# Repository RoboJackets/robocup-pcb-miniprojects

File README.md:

# Robocup 2026 Onboarding Project

## Description

This is the main repo for the 2026 onboarding season of Robojackets Robocup.

## Setup

Have ONE member of your team do this:

```sh
git clone https://github.com/RoboJackets/robocup-pcb-miniprojects
cd robocup-pcb-miniprojects
git checkout -b <your-team-name>
git push -u origin <your-team-name>
```

Now ALL members can:

```sh
git clone https://github.com/RoboJackets/robocup-pcb-miniprojects
cd robocup-pcb-miniprojects
git checkout <your-team-name>
```

This branch is where all work for your project should be done. Do not attempt to modify main, and especially do not try to modify other teams' branches.

## Overview

Your task is to create a daisy-chained sensor suite. Powered by the RP2040, this should be able to take a data packet from an SPI input, add to this packet, and pass it to the next board via SPI. Information for this packet is to be collected from the six distinct I2C devices on the board.

### PCB
Your KiCAD project folder and all other relevant files should be stored in [pcb](/pcb/).

See the [README](/pcb/README.md) for specific information.

### Firmware
Your Pico SDK project folder and all other relevant files should be stored in [firmware](/firmware/).

See the [README](/firmware/README.md) for specific information.

### Documentation

All live documentation (Hardware Reference Manuals, Technical Overviews, etc) should be stored in your team's drive folder which can be found [HERE](https://drive.google.com/drive/folders/1aSuq1g-BM3DlAOSG3E911sSWYeNv8i6k?usp=drive_link).

Start by copying the two template files from the project template folder [HERE](https://drive.google.com/drive/folders/1uaQHIUm1E482NEQLdI7As42oW3_wIS3i?usp=drive_link).

## Additional Notes

Project updates will be added here as needed

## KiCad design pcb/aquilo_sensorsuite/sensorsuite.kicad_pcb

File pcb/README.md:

# Daisy-Chained Sensor Suite PCB

## Overview

You will be planning, designing, and laying out the PCB for a daisy-chainable sensor suite. The core features of this board will be a RP2040 MCU, Micro USB programming/power input, SPI I/O, and six I2C peripherals.

## Requirements

Additional design specifications can be found in the Hardware Reference Manual (HRM).

1. Documentation
    - While most major parts are pre-selected for you, the documentation for these has not been. You will need to finish filling out the missing sections in the HRM for each component.
    - If you add any new components with a major impact on the final product, make sure to include them as well
    - Overall, keep your HRM as up to date as possible with as much important information as possible so your firmware team can progress along side you
2. PCB
    - Must be manufacturable
        - See JLCPCB capabilities [HERE](https://jlcpcb.com/capabilities/pcb-capabilities)
        - *Hint hint nudge nudge an option for board settings is to import from another board, and Robocup might have boards with similar design requirements [HERE](https://github.com/RoboJackets/robocup-pcb)*
    - Four layers max
        - Going below four is not recommended
    - Size
        - 80mm X 50mm
    - Must pass DRC
        - Will be checked with the Robocup standard DRC suite (if you followed the hint this likely will not be an issue)
    - Must consider signal integrity
    - Must have a legible and correct silkscreen
        - Labels by components or otherwise noted
        - Location for serial number
        - Identifier for all those who worked on it
        - Bonus points for fitting the Robojackets logo
    - Must meet overall required specifications
    - Must have 4 mounting holes (M2)
3. Schematic
    - Must utilize a hierarchy of sheets
        - Do not even ask for a design review of a schematic all crammed on one sheet it is not feasible for the expected complexity
        - Also do not excessively break into sub-sheets, consider what is seperate/repeatable enough to place in a sub-sheet.
    - Notate important characteristics in the schematic
        - General comments
        - Section functionality
        - Placement location requirements
        - Component relevant information
        - The less you have to check the HRM the better
    - Must fill out all sheet information in the right corner
        - Include an additional note for designer name
    - Symbol fields
        - You must fill out all default fields of major components. Non-specialized passives just need footprint and value
        - You must add the field "Vendor P/N" to every specific component with the value set to the Digikey part number
    - When you need to make/import new symbols/footprints/3D models, add them to a new custom library called "local" and store their files if needed in [lib](./lib/)
    - Maintain neatness and readability throughout the schematic
        - General signal flow should go left to right
        - Favor wire net labels over long track wires/grouped outputs
        - Group components by relation/usage
4. Power
    - Power must be able to come from both the USB port and the previous board's SPI line and they must never touch
        - See power MUXing
    - Your power must have appropriate protection for issues such as reverse voltage, ESD, shorts, etc.
    - Your total power draw, and expected power draw for six connected boards must be noted in your schematic and reflected in your protection circuits 
        - Note only one board with an LED array will be active at once
    - There must be some indication that power is connected to the board
5. I2C Devices
    - Must have all six I2C devices and their complementary circuits
        1. IMU
        2. Temperature Sensor
        3. Hall Effect Sensor
        4. GPIO expander
            - Connected to 8 switch DIP switch
            - Resistor network pullup
        5. Color Sensor
        6. LED PWM Controller
            - 8 RGB LEDs
    - Each device must have have different I2C lines
        - However they can share I2C buses
    - Do not use interrupt lines
        - Leave safely disconnected per design requirements
6. Interface
    - Must have at least two general purpose buttons
    - Must have at least three general purpose LEDs
    - Must have test points for all important voltage/signal sources
7. Overall
    - All parts must be in-stock at Digikey at time of completion
        - Yes, if stock runs out during the duration of the project this is still on you to catch
        - You can disregard this rule for parts from the Part Selection specification

## Specifications

### Part Selection

These parts have already been selected for you

- MCU: RP2040
    - 2648-SC0914(13)TR-ND
- 2MB Flash: W25Q16JVUXIQ TR
    - 256-W25Q16JVUXIQTR-ND
- 12MHz Crystal: ABM8-272-T3
    - 535-ABM8-272-T3TR-ND
- IMU: ICM-42605
    - 1428-1152-2-ND
- Color Sensor: VEML3328
    - 751-VEML3328TR-ND
- Hall Effect Sensor: TMAG5273A2QDBVR
    - 296-TMAG5273A2QDBVRTR-ND
- Temperature Sensor: LM75ADP
    - 568-4227-1-ND
- GPIO Expander: TCA9534PWR
    - 296-40574-2-ND
- DIP Switch: DS01C-254-L-08BE
    - 2223-DS01C-254-L-08BE-ND
- 10kOhm Resistor Network: YC158TJR-0710KL
    - 13-YC158TJR-0710KLTR-ND
- LED Controller: IS31FL3254-QFLS4-TR
    - 2521-IS31FL3254-QFLS4-TR-ND
- RGB LEDs: CLMVC-FKA-CL1D1L71BB7C3C3
    - CLMVC-FKA-CL1D1L71BB7C3C3TR-ND
- Micro USB Connector: 10118194-0001LF
    - 609-4618-2-ND
- SPI Connector: S6B-PH-K-S
    - 455-1723-ND
- 3.3V Linear Regulator: AP2112K-3.3
    - AP2112K-3.3TRG1DITR-ND
- OR Controller: LM66100DCKR
    - 296-53541-2-ND
- General Purpose LEDs (3)
    - 0603 LEDs
- General Purpose Buttons (2): SKRPABE010
    - 4809-SKRPABE010TR-ND

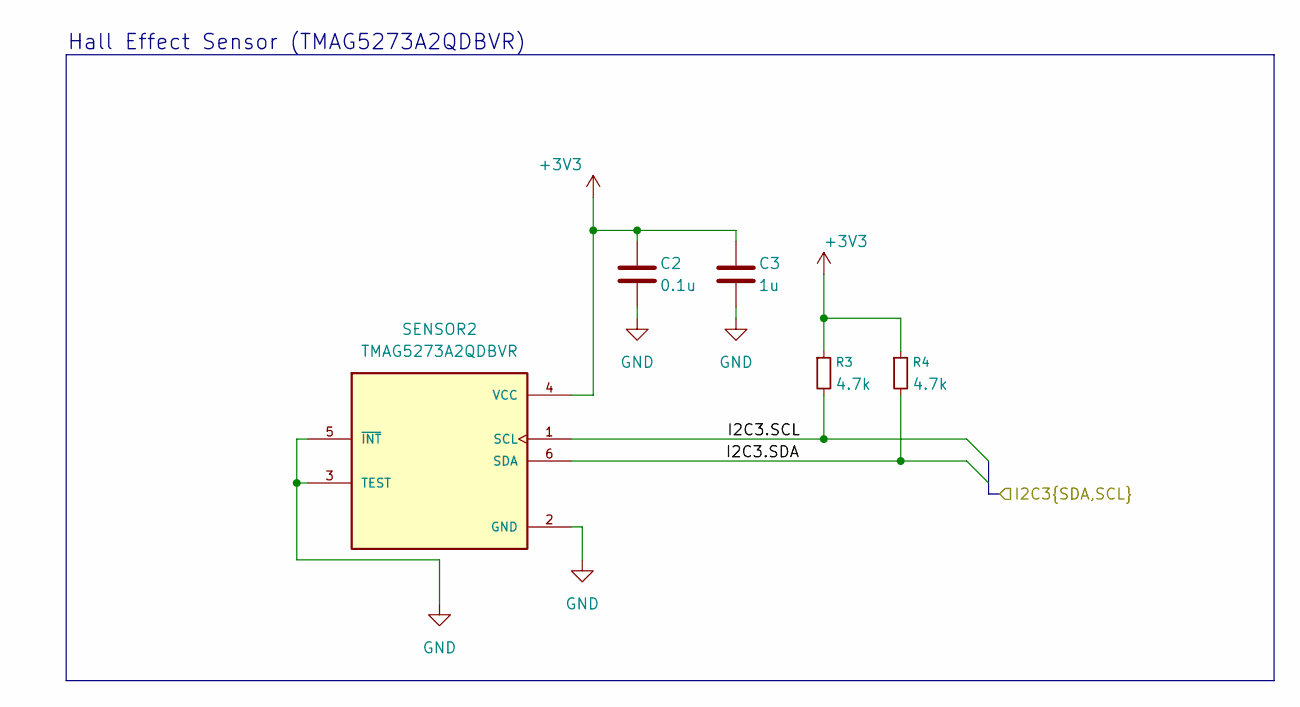
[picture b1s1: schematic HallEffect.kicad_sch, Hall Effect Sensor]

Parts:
C2: 0.1u; C_0402_1005Metric; Manufacturer P/N 0402B104K160HI
C3: 1u; C_0402_1005Metric; Manufacturer P/N 0402W105M6R3HI
R3, R4: 4.7k; R_0402_1005Metric; Manufacturer P/N RK73H1ETTP4701F
SENSOR2: TMAG5273A2QDBVR; SOT95P280X140-6N; Manufacturer P/N TMAG5273A2QDBVR

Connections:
+3V3: C2.1, C3.1, R3.1, R4.1, SENSOR2.4 (VCC); also elsewhere on the board
/Hall Effect Sensor/I2C3.SCL: R3.2, SENSOR2.1 (SCL); also elsewhere on the board
/Hall Effect Sensor/I2C3.SDA: R4.2, SENSOR2.6 (SDA); also elsewhere on the board
GND: C2.2, C3.2, SENSOR2.2 (GND), SENSOR2.3 (TEST), SENSOR2.5 (~INT); also elsewhere on the board

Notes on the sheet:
Hall Effect Sensor (TMAG5273A2QDBVR)

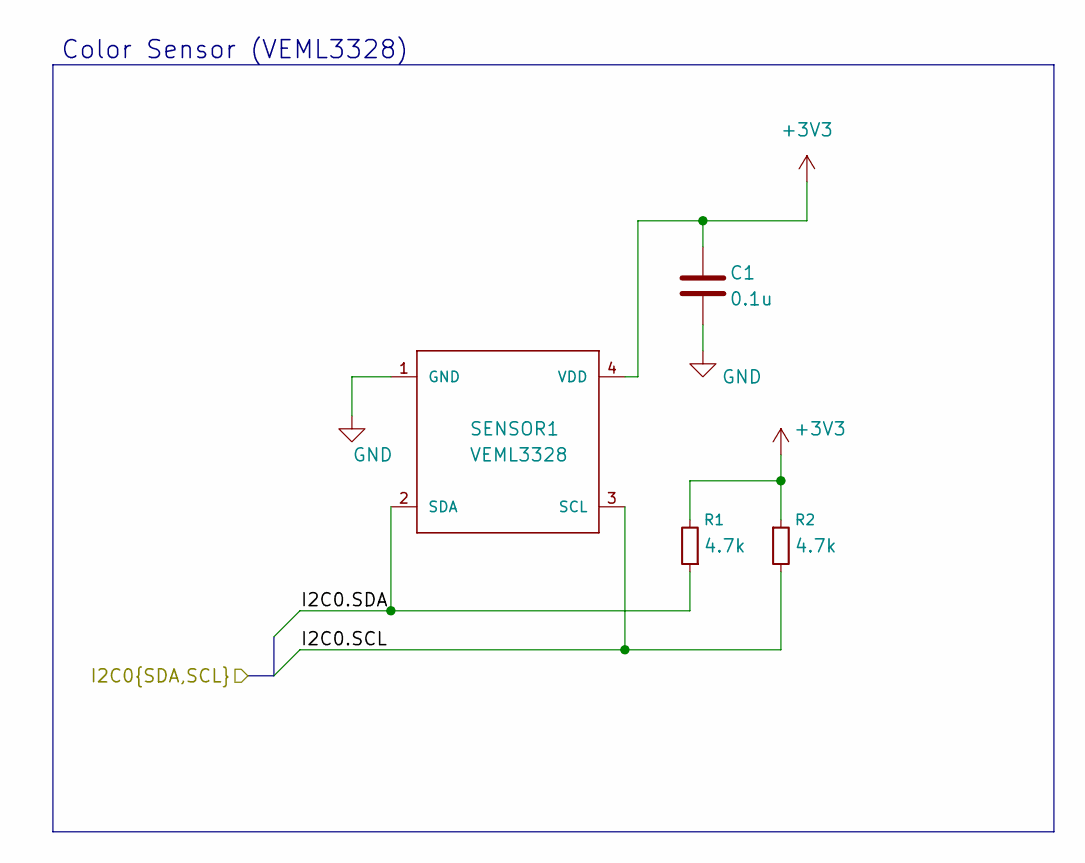
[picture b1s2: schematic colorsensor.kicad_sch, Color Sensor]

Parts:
C1: 0.1u; C_0402_1005Metric; Manufacturer P/N 0402B104K160HI
R1, R2: 4.7k; R_0402_1005Metric; Manufacturer P/N RK73H1ETTP4701F
SENSOR1: VEML3328; Manufacturer P/N VEML3328

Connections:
+3V3: C1.1, R1.2, R2.1, SENSOR1.4 (VDD); also elsewhere on the board
/Color Sensor/I2C0.SCL: R2.2, SENSOR1.3 (SCL); also elsewhere on the board
/Color Sensor/I2C0.SDA: R1.1, SENSOR1.2 (SDA); also elsewhere on the board
GND: C1.2, SENSOR1.1 (GND); also elsewhere on the board

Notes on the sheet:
Color Sensor (VEML3328)

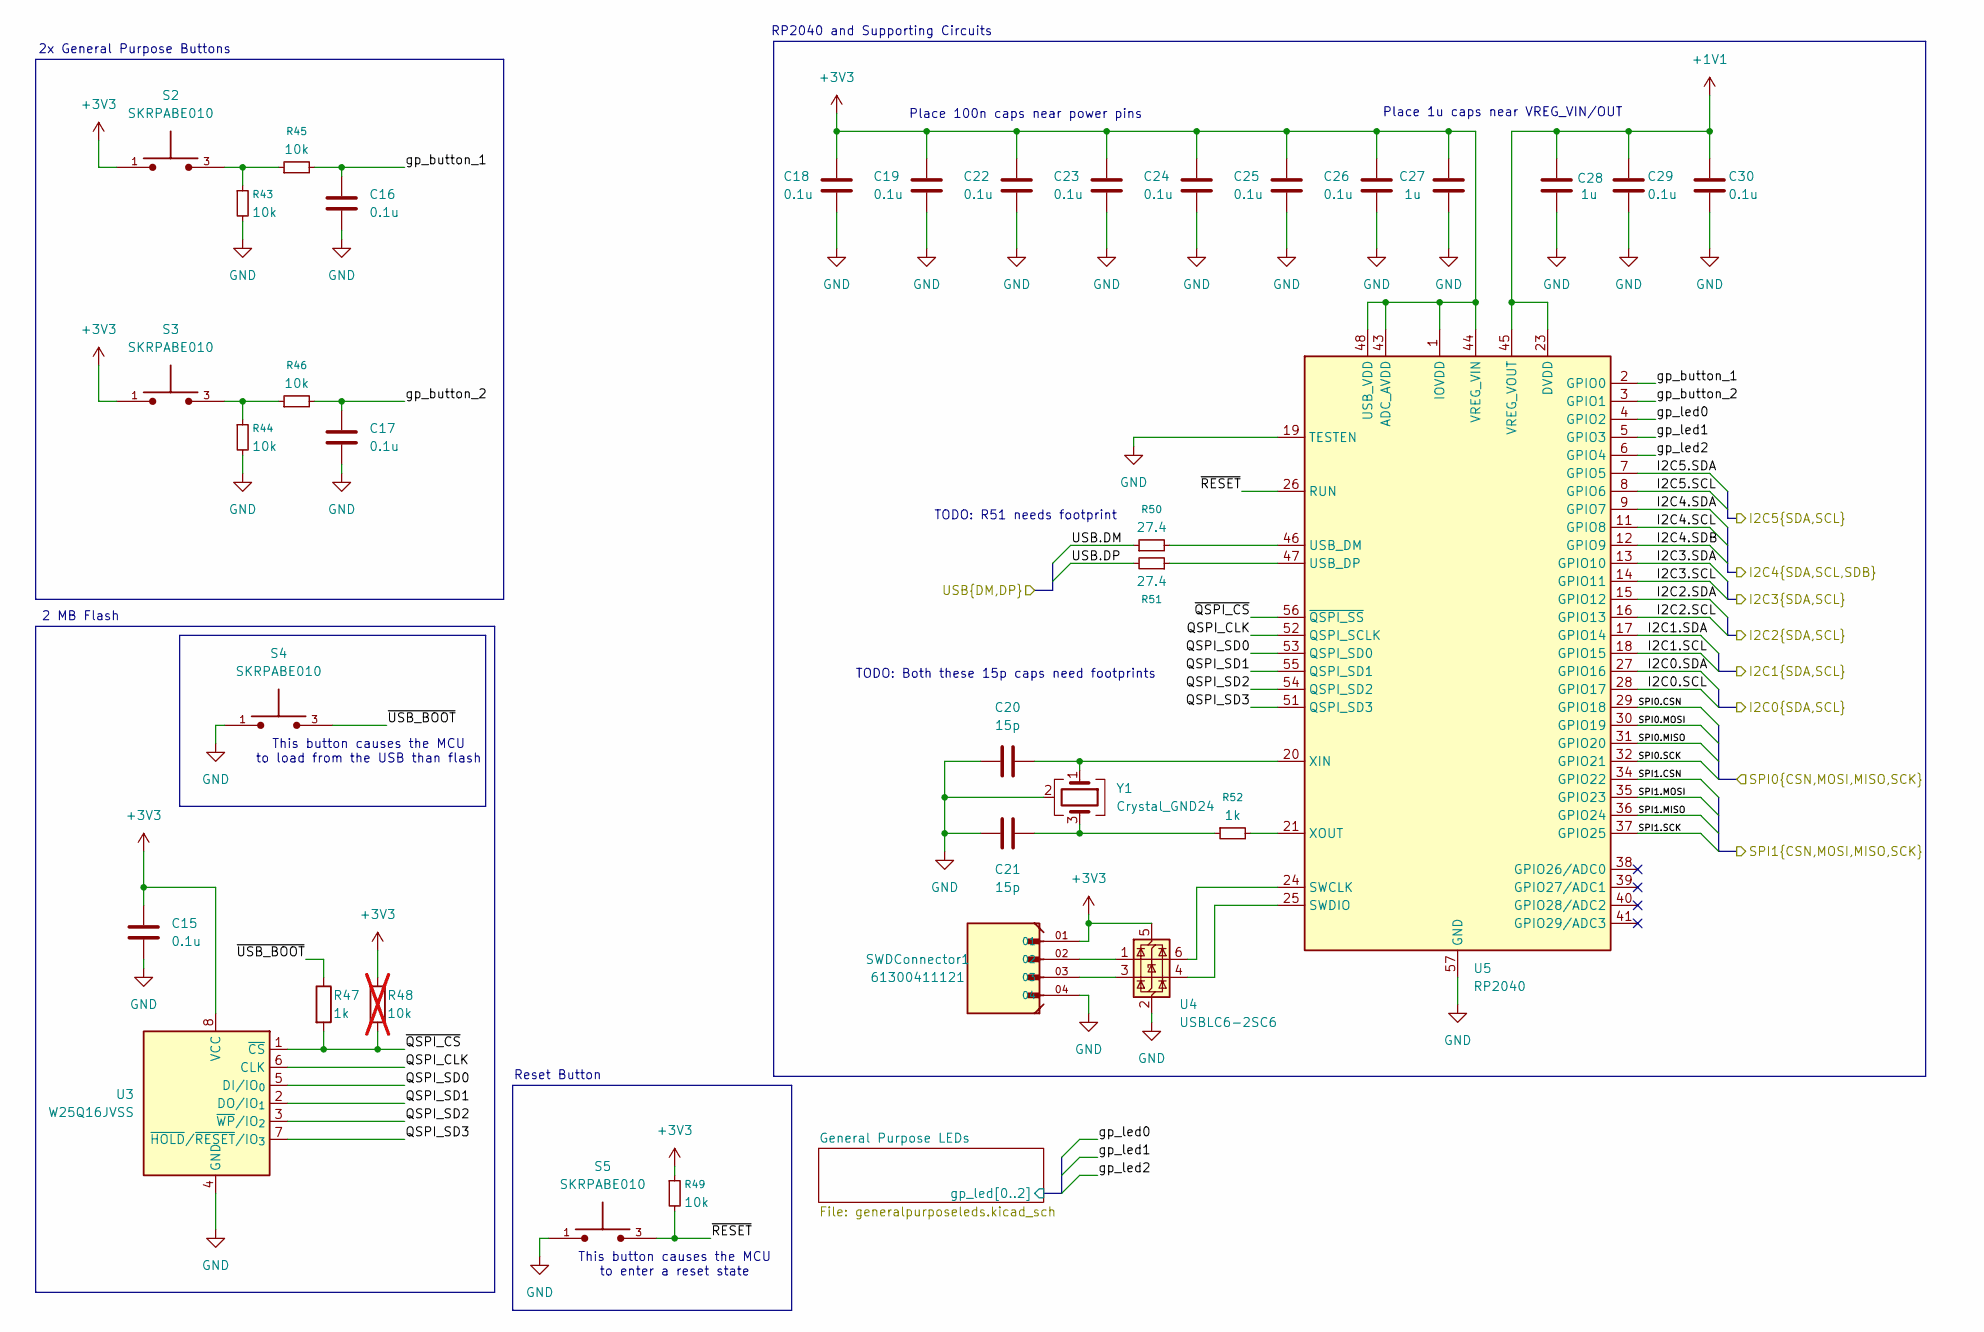
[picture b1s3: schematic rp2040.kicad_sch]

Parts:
C15, C16, C17, C18, C19, C22, C23, C24, C25, C26, C29, C30: 0.1u; C_0402_1005Metric; Manufacturer P/N 0402B104K160HI
C20, C21: 15p; C_0402_1005Metric; Manufacturer P/N GRM1555C1H150JA01D
C27, C28: 1u; C_0402_1005Metric; Manufacturer P/N 0402W105M6R3HI
R43, R44, R45, R46, R49: 10k; R_0402_1005Metric; Manufacturer P/N RK73H1ETTP1002F
R47, R52: 1k; R_0402_1005Metric; Manufacturer P/N RK73H1ETTP1001F
R48: 10k; R_0402_1005Metric; Manufacturer P/N RK73H1ETTP1002F; not fitted
R50, R51: 27.4; R_0402_1005Metric; Manufacturer P/N RC0402FR-0727R4L
S2, S3, S4, S5: SKRPABE010; SW_SKRPABE010; Manufacturer P/N SKRPABE010
SWDConnector1: 61300411121; WURTH_61300411121; Manufacturer P/N 61300411121
U3: W25Q16JVSS; SOIC-8_5.3x5.3mm_P1.27mm; Manufacturer P/N W25Q16JVUXIQ TR
U4: USBLC6-2SC6; SOT-23-6; Manufacturer P/N USBLC6-2SC6
U5: RP2040; QFN-56-1EP_7x7mm_P0.4mm_EP3.2x3.2mm; Manufacturer P/N SC0914(13)
Y1: Crystal_GND24; Crystal_SMD_Abracon_ABM8AIG-4Pin_3.2x2.5mm; Manufacturer P/N ABM8-272-T3

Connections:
+1V1: C28.1, C29.1, C30.1, U5.23 (DVDD), U5.45 (VREG_VOUT), U5.50 (DVDD)
+3V3: C15.1, C18.1, C19.1, C22.1, C23.1, C24.1, C25.1, C26.1, C27.1, R48.1, R49.1, S2.1, S2.2, S3.1, S3.2, SWDConnector1.01, U3.8 (VCC), U4.5 (VBUS), U5.1 (IOVDD), U5.10 (IOVDD), U5.22 (IOVDD), U5.33 (IOVDD), U5.42 (IOVDD), U5.43 (ADC_AVDD), U5.44 (VREG_VIN), U5.48 (USB_VDD), U5.49 (IOVDD); also elsewhere on the board
/Color Sensor/I2C0.SCL: U5.28 (GPIO17); also elsewhere on the board
/Color Sensor/I2C0.SDA: U5.27 (GPIO16); also elsewhere on the board
/GPIO Expander/I2C2.SCL: U5.16 (GPIO13); also elsewhere on the board
/GPIO Expander/I2C2.SDA: U5.15 (GPIO12); also elsewhere on the board
/Hall Effect Sensor/I2C3.SCL: U5.14 (GPIO11); also elsewhere on the board
/Hall Effect Sensor/I2C3.SDA: U5.13 (GPIO10); also elsewhere on the board
/IMU/I2C5.SCL: U5.8 (GPIO6); also elsewhere on the board
/IMU/I2C5.SDA: U5.7 (GPIO5); also elsewhere on the board
/LED Controller/I2C4.SCL: U5.11 (GPIO8); also elsewhere on the board
/LED Controller/I2C4.SDA: U5.9 (GPIO7); also elsewhere on the board
/LED Controller/I2C4.SDB: U5.12 (GPIO9); also elsewhere on the board
/Power/SPI0.CSN: U5.29 (GPIO18); also elsewhere on the board
/Power/SPI0.MISO: U5.31 (GPIO20); also elsewhere on the board
/Power/SPI0.MOSI: U5.30 (GPIO19); also elsewhere on the board
/Power/SPI0.SCK: U5.32 (GPIO21); also elsewhere on the board
/Power/SPI1.CSN: U5.34 (GPIO22); also elsewhere on the board
/Power/SPI1.MISO: U5.36 (GPIO24); also elsewhere on the board
/Power/SPI1.MOSI: U5.35 (GPIO23); also elsewhere on the board
/Power/SPI1.SCK: U5.37 (GPIO25); also elsewhere on the board
/Power/USB.DM: R50.1; also elsewhere on the board
/Power/USB.DP: R51.2; also elsewhere on the board
/Temperature Sensor/I2C1.SCL: U5.18 (GPIO15); also elsewhere on the board
/Temperature Sensor/I2C1.SDA: U5.17 (GPIO14); also elsewhere on the board
/rp2040/General Purpose LEDs/gp_led0: U5.4 (GPIO2); also elsewhere on the board
/rp2040/General Purpose LEDs/gp_led1: U5.5 (GPIO3); also elsewhere on the board
/rp2040/General Purpose LEDs/gp_led2: U5.6 (GPIO4); also elsewhere on the board
/rp2040/QSPI_CLK: U3.6 (CLK), U5.52 (QSPI_SCLK)
/rp2040/QSPI_SD0: U3.5 (DI/IO_{0}), U5.53 (QSPI_SD0)
/rp2040/QSPI_SD1: U3.2 (DO/IO_{1}), U5.55 (QSPI_SD1)
/rp2040/QSPI_SD2: U3.3 (~WP/IO_{2}), U5.54 (QSPI_SD2)
/rp2040/QSPI_SD3: U3.7 (~HOLD/~RESET/IO_{3}), U5.51 (QSPI_SD3)
/rp2040/gp_button_1: C16.1, R45.2, U5.2 (GPIO0)
/rp2040/gp_button_2: C17.1, R46.2, U5.3 (GPIO1)
/rp2040/~QSPI_CS: R47.2, R48.2, U3.1 (~CS), U5.56 (~QSPI_SS)
/rp2040/~RESET: R49.2, S5.3, S5.4, U5.26 (RUN)
/rp2040/~USB_BOOT: R47.1, S4.3, S4.4
GND: C15.2, C16.2, C17.2, C18.2, C19.2, C20.1, C21.1, C22.2, C23.2, C24.2, C25.2, C26.2, C27.2, C28.2, C29.2, C30.2, R43.2, R44.2, S4.1, S4.2, S5.1, S5.2, SWDConnector1.04, U3.4 (GND), U4.2 (GND), U5.19 (TESTEN), U5.57 (GND), Y1.2 (G), Y1.4 (G); also elsewhere on the board
unnamed: C21.2, R52.1, Y1.3
unnamed: R43.1, R45.1, S2.3, S2.4
unnamed: R44.1, R46.1, S3.3, S3.4
unnamed: SWDConnector1.02, U4.1 (I/O1)
unnamed: SWDConnector1.03, U4.3 (I/O2)
unnamed: U4.6 (I/O1), U5.24 (SWCLK)
unnamed: U4.4 (I/O2), U5.25 (SWDIO)
unnamed: R50.2, U5.46 (USB_DM)
unnamed: R51.1, U5.47 (USB_DP)
unnamed: C20.2, U5.20 (XIN), Y1.1
unnamed: R52.2, U5.21 (XOUT)

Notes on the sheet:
2x General Purpose Buttons
TODO: R51 needs footprint
Reset Button
This button causes the MCU to load from the USB than flash
TODO: Both these 15p caps need footprints
2 MB Flash
Place 1u caps near VREG_VIN/OUT
RP2040 and Supporting Circuits
This button causes the MCU to enter a reset state
Place 100n caps near power pins

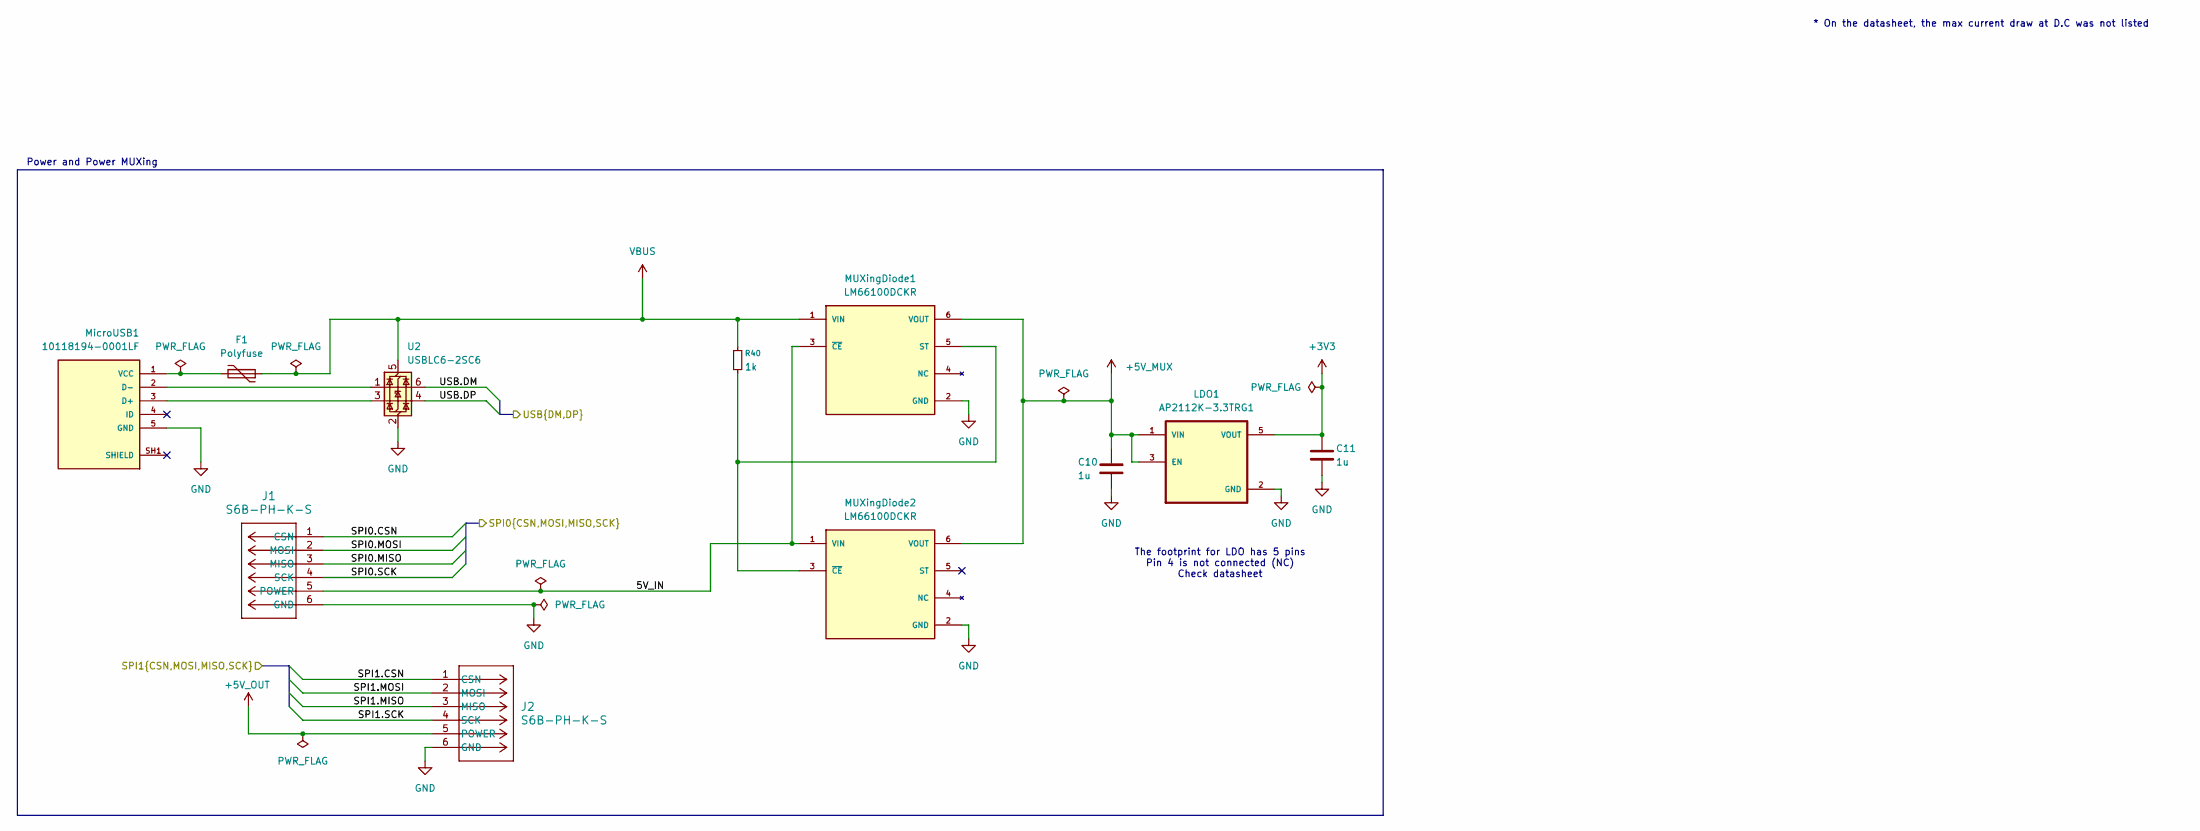
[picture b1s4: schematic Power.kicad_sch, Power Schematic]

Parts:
C10, C11: 1u; C_0402_1005Metric; Manufacturer P/N 0402W105M6R3HI
F1: Polyfuse; Fuse_1206_3216Metric; Manufacturer P/N MPTS1206L050
J1, J2: S6B-PH-K-S; JST_S6B-PH-K-S_LF__SN_; Manufacturer P/N S6B-PH-K-S
LDO1: AP2112K-3.3TRG1; SOT95P285X140-5N; Manufacturer P/N AP2112K-3.3TRG1
MUXingDiode1, MUXingDiode2: LM66100DCKR; SOT65P210X110-6N; Manufacturer P/N LM66100DCKR
MicroUSB1: 10118194-0001LF; AMPHENOL_10118194-0001LF; Manufacturer P/N 10118194-0001LF
R40: 1k; R_0402_1005Metric; Manufacturer P/N RK73H1ETTP1001F
U2: USBLC6-2SC6; SOT-23-6; Manufacturer P/N USBLC6-2SC6

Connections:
+3V3: C11.1, LDO1.5 (VOUT); also elsewhere on the board
+5V_MUX: C10.1, LDO1.1 (VIN), LDO1.3 (EN), MUXingDiode1.6 (VOUT), MUXingDiode2.6 (VOUT)
+5V_OUT: J2.5 (POWER)
/Power/5V_IN: J1.5 (POWER), MUXingDiode1.3 (~CE), MUXingDiode2.1 (VIN)
/Power/SPI0.CSN: J1.1 (CSN); also elsewhere on the board
/Power/SPI0.MISO: J1.3 (MISO); also elsewhere on the board
/Power/SPI0.MOSI: J1.2 (MOSI); also elsewhere on the board
/Power/SPI0.SCK: J1.4 (SCK); also elsewhere on the board
/Power/SPI1.CSN: J2.1 (CSN); also elsewhere on the board
/Power/SPI1.MISO: J2.3 (MISO); also elsewhere on the board
/Power/SPI1.MOSI: J2.2 (MOSI); also elsewhere on the board
/Power/SPI1.SCK: J2.4 (SCK); also elsewhere on the board
/Power/USB.DM: U2.6 (I/O1); also elsewhere on the board
/Power/USB.DP: U2.4 (I/O2); also elsewhere on the board
GND: C10.2, C11.2, J1.6 (GND), J2.6 (GND), LDO1.2 (GND), MUXingDiode1.2 (GND), MUXingDiode2.2 (GND), MicroUSB1.5 (GND), U2.2 (GND); also elsewhere on the board
unnamed: MUXingDiode1.5 (ST), MUXingDiode2.3 (~CE), R40.2
unnamed: MicroUSB1.3 (D+), U2.3 (I/O2)
unnamed: MicroUSB1.2 (D-), U2.1 (I/O1)
unnamed: F1.2, MicroUSB1.1 (VCC)
VBUS: F1.1, MUXingDiode1.1 (VIN), R40.1, U2.5 (VBUS)

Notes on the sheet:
The footprint for LDO has 5 pins Pin 4 is not connected (NC) Check datasheet
Power and Power MUXing
* On the datasheet, the max current draw at D.C was not listed

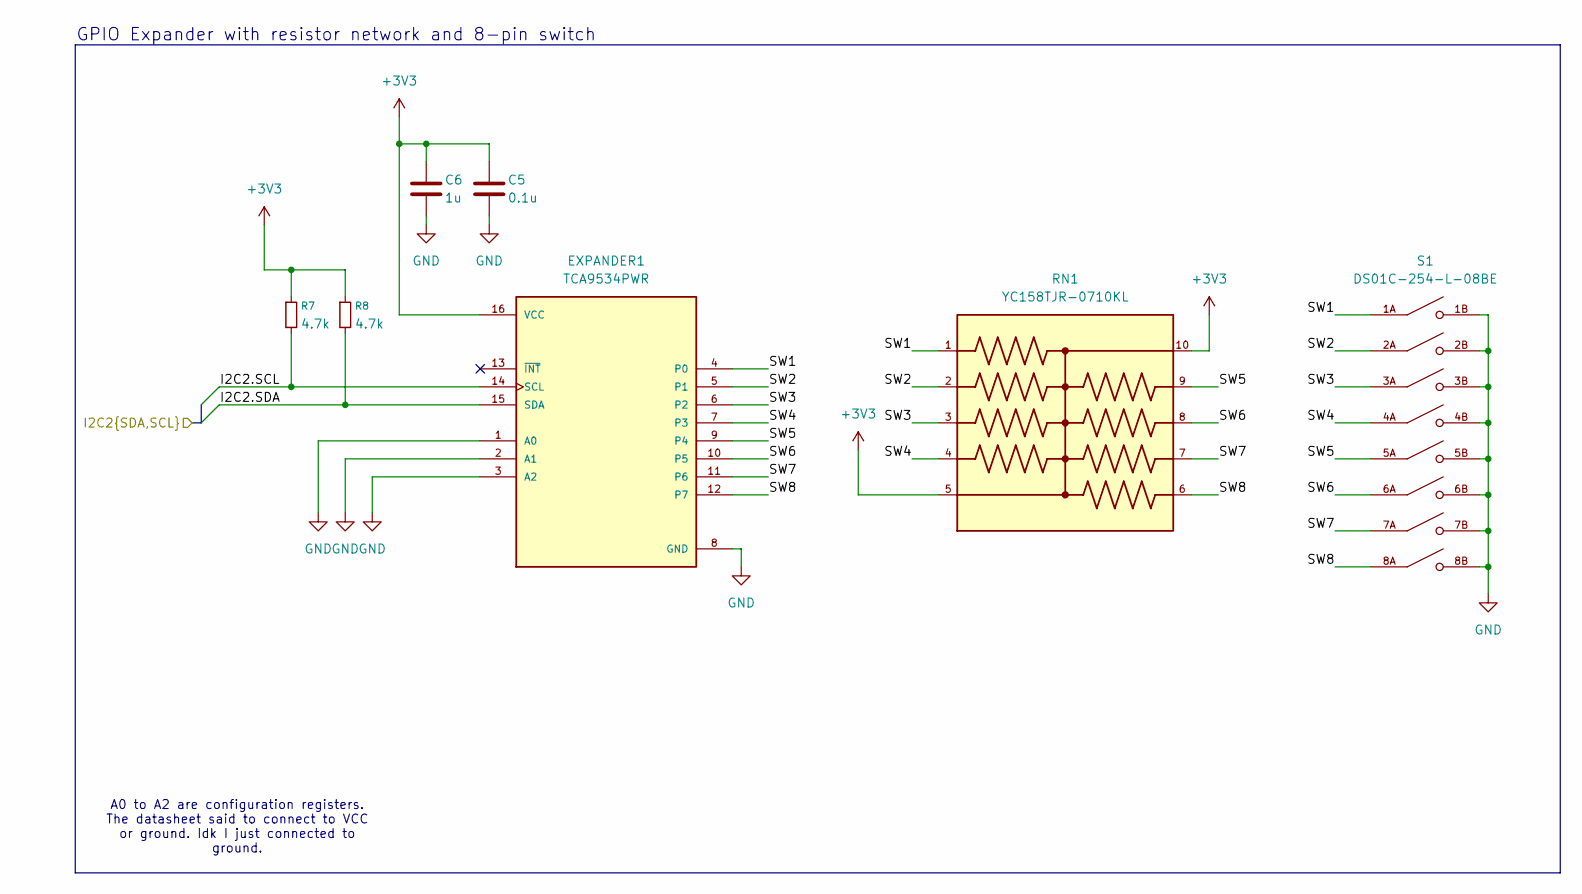
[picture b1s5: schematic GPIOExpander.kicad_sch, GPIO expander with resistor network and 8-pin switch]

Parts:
C5: 0.1u; C_0402_1005Metric; Manufacturer P/N 0402B104K160HI
C6: 1u; C_0402_1005Metric; Manufacturer P/N 0402W105M6R3HI
EXPANDER1: TCA9534PWR; SOP65P640X120-16N; Manufacturer P/N TCA9534PWR
R7, R8: 4.7k; R_0402_1005Metric; Manufacturer P/N RK73H1ETTP4701F
RN1: YC158TJR-0710KL; RESCAXE64P320X160X70-10N; Manufacturer P/N YC158TJR-0710KL
S1: DS01C-254-L-08BE; SW_DS01C-254-L-08BE; Manufacturer P/N DS01C-254-L-08BE

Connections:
+3V3: C5.1, C6.1, EXPANDER1.16 (VCC), R7.1, R8.1, RN1.5, RN1.10; also elsewhere on the board
/GPIO Expander/I2C2.SCL: EXPANDER1.14 (SCL), R7.2; also elsewhere on the board
/GPIO Expander/I2C2.SDA: EXPANDER1.15 (SDA), R8.2; also elsewhere on the board
/GPIO Expander/SW1: EXPANDER1.4 (P0), RN1.1, S1.1A
/GPIO Expander/SW2: EXPANDER1.5 (P1), RN1.2, S1.2A
/GPIO Expander/SW3: EXPANDER1.6 (P2), RN1.3, S1.3A
/GPIO Expander/SW4: EXPANDER1.7 (P3), RN1.4, S1.4A
/GPIO Expander/SW5: EXPANDER1.9 (P4), RN1.9, S1.5A
/GPIO Expander/SW6: EXPANDER1.10 (P5), RN1.8, S1.6A
/GPIO Expander/SW7: EXPANDER1.11 (P6), RN1.7, S1.7A
/GPIO Expander/SW8: EXPANDER1.12 (P7), RN1.6, S1.8A
GND: C5.2, C6.2, EXPANDER1.1 (A0), EXPANDER1.2 (A1), EXPANDER1.3 (A2), EXPANDER1.8 (GND), S1.1B, S1.2B, S1.3B, S1.4B, S1.5B, S1.6B, S1.7B, S1.8B; also elsewhere on the board

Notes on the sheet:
A0 to A2 are configuration registers. The datasheet said to connect to VCC or ground. Idk I just connected to ground.
GPIO Expander with resistor network and 8-pin switch

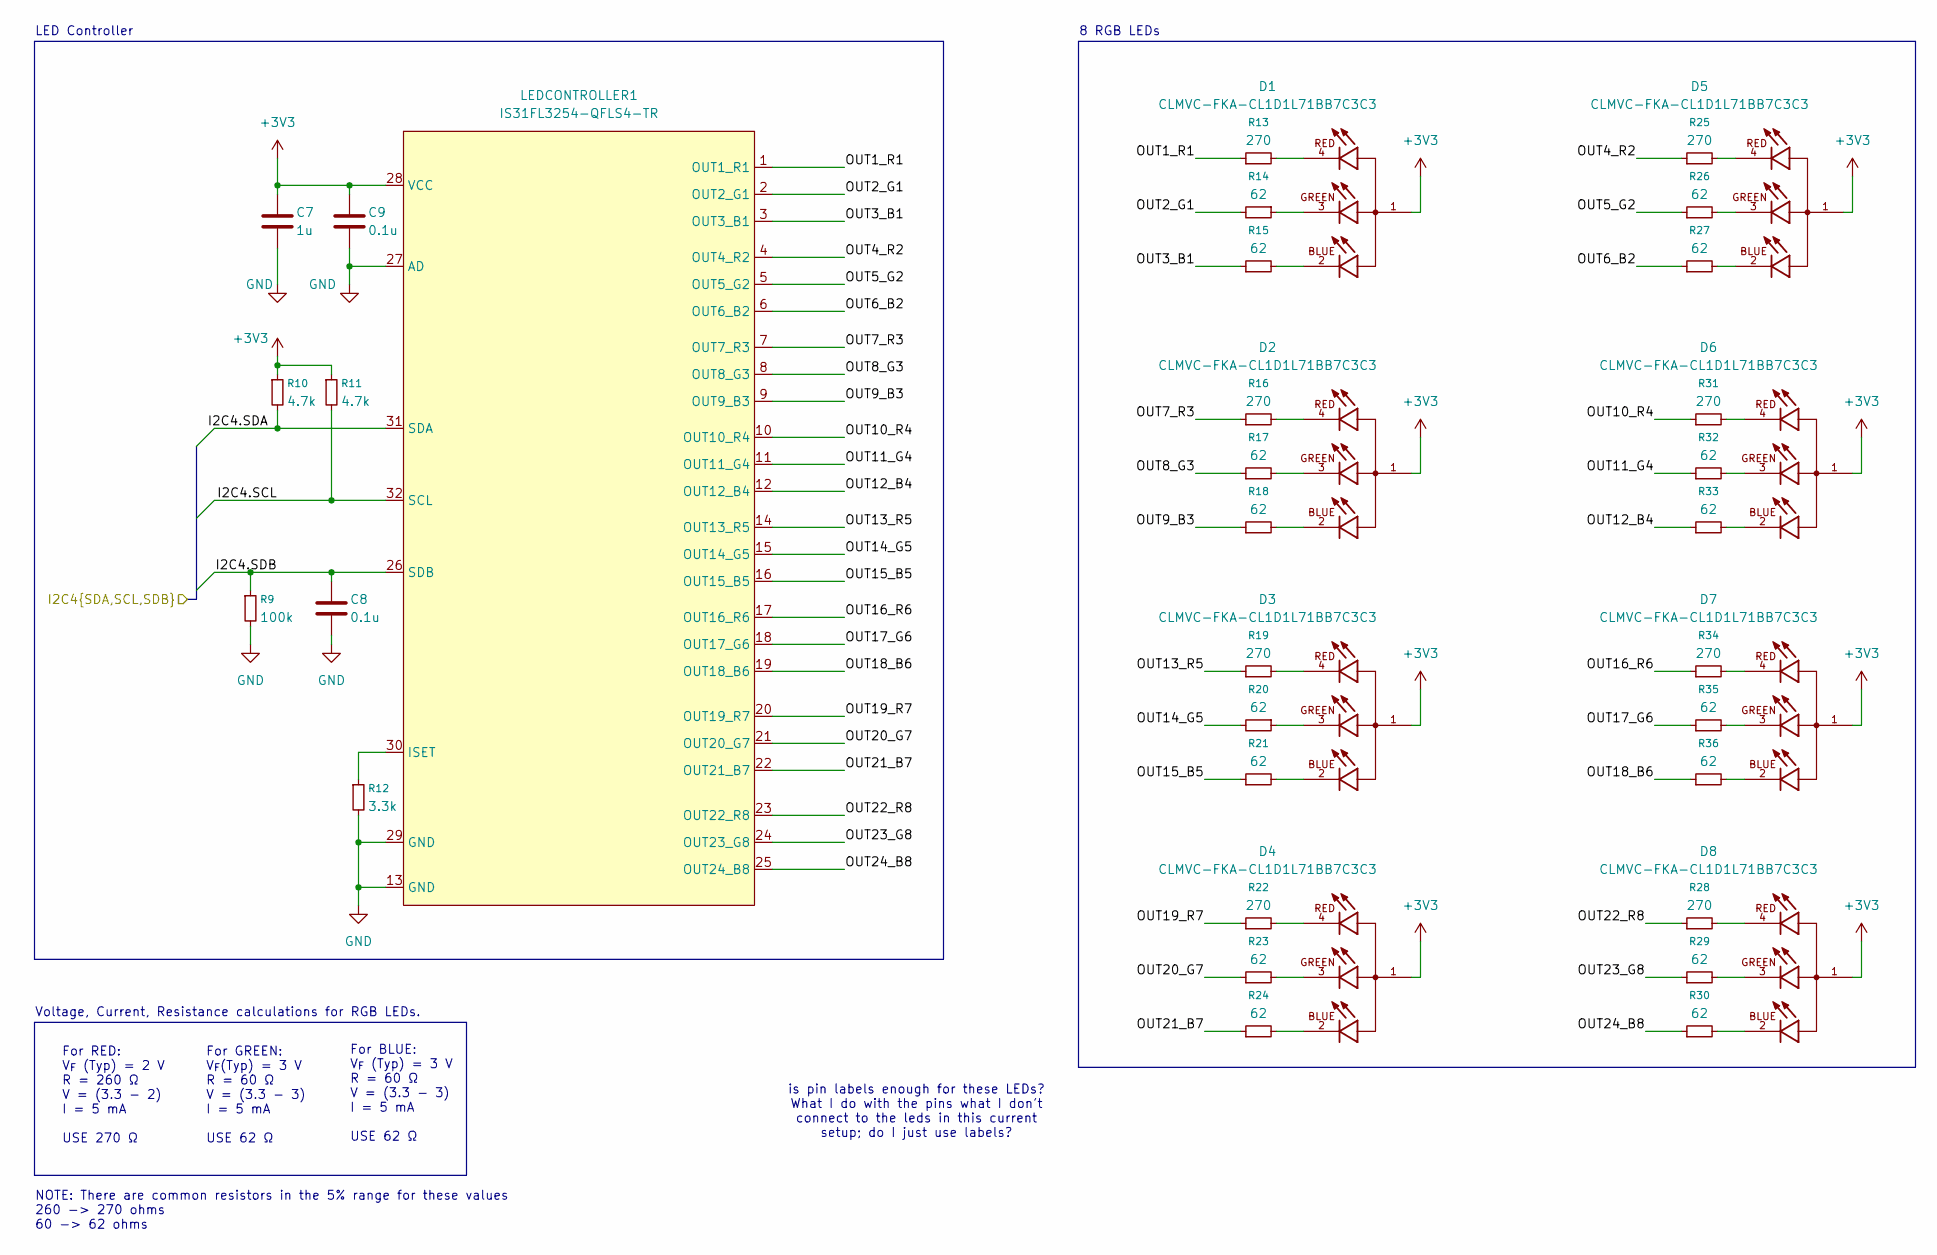
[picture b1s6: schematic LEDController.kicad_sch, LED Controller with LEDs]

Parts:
C7: 1u; C_0402_1005Metric; Manufacturer P/N 0402W105M6R3HI
C8, C9: 0.1u; C_0402_1005Metric; Manufacturer P/N 0402B104K160HI
D1, D2, D3, D4, D5, D6, D7, D8: CLMVC-FKA-CL1D1L71BB7C3C3; LED_CLMVC-FKA-CL1D1L71BB7C3C3; Manufacturer P/N CLMVC-FKA-CL1D1L71BB7C3C3
LEDCONTROLLER1: IS31FL3254-QFLS4-TR; 0; Manufacturer P/N IS31FL3254-QFLS4-TR
R9: 100k; R_0402_1005Metric; Manufacturer P/N ERJ-2GEJ104X
R10, R11: 4.7k; R_0402_1005Metric; Manufacturer P/N RK73H1ETTP4701F
R12: 3.3k; R_0402_1005Metric; Manufacturer P/N RC0402JR-073K3L
R13, R16, R19, R22, R25, R28, R31, R34: 270; R_0402_1005Metric; Manufacturer P/N ERJ-2GEJ271X
R14, R15, R17, R18, R20, R21, R23, R24, R26, R27, R29, R30, R32, R33, R35, R36: 62; R_0402_1005Metric; Manufacturer P/N ERJ-2GEJ620X

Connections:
+3V3: C7.1, C9.1, D1.1, D2.1, D3.1, D4.1, D5.1, D6.1, D7.1, D8.1, LEDCONTROLLER1.28 (VCC), R10.1, R11.1; also elsewhere on the board
/LED Controller/I2C4.SCL: LEDCONTROLLER1.32 (SCL), R11.2; also elsewhere on the board
/LED Controller/I2C4.SDA: LEDCONTROLLER1.31 (SDA), R10.2; also elsewhere on the board
/LED Controller/I2C4.SDB: C8.1, LEDCONTROLLER1.26 (SDB), R9.1; also elsewhere on the board
/LED Controller/OUT1_R1: LEDCONTROLLER1.1 (OUT1_R1), R13.1
/LED Controller/OUT2_G1: LEDCONTROLLER1.2 (OUT2_G1), R14.2
/LED Controller/OUT3_B1: LEDCONTROLLER1.3 (OUT3_B1), R15.1
/LED Controller/OUT4_R2: LEDCONTROLLER1.4 (OUT4_R2), R25.1
/LED Controller/OUT5_G2: LEDCONTROLLER1.5 (OUT5_G2), R26.1
/LED Controller/OUT6_B2: LEDCONTROLLER1.6 (OUT6_B2), R27.1
/LED Controller/OUT7_R3: LEDCONTROLLER1.7 (OUT7_R3), R16.1
/LED Controller/OUT8_G3: LEDCONTROLLER1.8 (OUT8_G3), R17.1
/LED Controller/OUT9_B3: LEDCONTROLLER1.9 (OUT9_B3), R18.1
/LED Controller/OUT10_R4: LEDCONTROLLER1.10 (OUT10_R4), R31.1
/LED Controller/OUT11_G4: LEDCONTROLLER1.11 (OUT11_G4), R32.1
/LED Controller/OUT12_B4: LEDCONTROLLER1.12 (OUT12_B4), R33.1
/LED Controller/OUT13_R5: LEDCONTROLLER1.14 (OUT13_R5), R19.1
/LED Controller/OUT14_G5: LEDCONTROLLER1.15 (OUT14_G5), R20.2
/LED Controller/OUT15_B5: LEDCONTROLLER1.16 (OUT15_B5), R21.1
/LED Controller/OUT16_R6: LEDCONTROLLER1.17 (OUT16_R6), R34.1
/LED Controller/OUT17_G6: LEDCONTROLLER1.18 (OUT17_G6), R35.1
/LED Controller/OUT18_B6: LEDCONTROLLER1.19 (OUT18_B6), R36.1
/LED Controller/OUT19_R7: LEDCONTROLLER1.20 (OUT19_R7), R22.1
/LED Controller/OUT20_G7: LEDCONTROLLER1.21 (OUT20_G7), R23.1
/LED Controller/OUT21_B7: LEDCONTROLLER1.22 (OUT21_B7), R24.1
/LED Controller/OUT22_R8: LEDCONTROLLER1.23 (OUT22_R8), R28.1
/LED Controller/OUT23_G8: LEDCONTROLLER1.24 (OUT23_G8), R29.1
/LED Controller/OUT24_B8: LEDCONTROLLER1.25 (OUT24_B8), R30.1
GND: C7.2, C8.2, C9.2, LEDCONTROLLER1.13 (GND), LEDCONTROLLER1.27 (AD), LEDCONTROLLER1.29 (GND), R9.2, R12.2; also elsewhere on the board
unnamed: D1.2, R15.2
unnamed: D1.3, R14.1
unnamed: D1.4, R13.2
unnamed: D2.2, R18.2
unnamed: D2.3, R17.2
unnamed: D2.4, R16.2
unnamed: D3.2, R21.2
unnamed: D3.3, R20.1
unnamed: D3.4, R19.2
unnamed: D4.2, R24.2
unnamed: D4.3, R23.2
unnamed: D4.4, R22.2
unnamed: D5.2, R27.2
unnamed: D5.3, R26.2
unnamed: D5.4, R25.2
unnamed: D6.2, R33.2
unnamed: D6.3, R32.2
unnamed: D6.4, R31.2
unnamed: D7.2, R36.2
unnamed: D7.3, R35.2
unnamed: D7.4, R34.2
unnamed: D8.2, R30.2
unnamed: D8.3, R29.2
unnamed: D8.4, R28.2
unnamed: LEDCONTROLLER1.30 (ISET), R12.1

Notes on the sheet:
For BLUE: V_{F} (Typ) = 3 V R = 60 Ω V = (3.3 - 3) I = 5 mA USE 62 Ω
LED Controller
is pin labels enough for these LEDs? What I do with the pins what I don't connect to the leds in this current setup; do I just use labels?
For RED: V_{F} (Typ) = 2 V R = 260 Ω V = (3.3 - 2) I = 5 mA USE 270 Ω
For GREEN: V_{F}(Typ) = 3 V R = 60 Ω V = (3.3 - 3) I = 5 mA USE 62 Ω
NOTE: There are common resistors in the 5% range for these values 260 -> 270 ohms 60 -> 62 ohms
8 RGB LEDs
Voltage, Current, Resistance calculations for RGB LEDs.

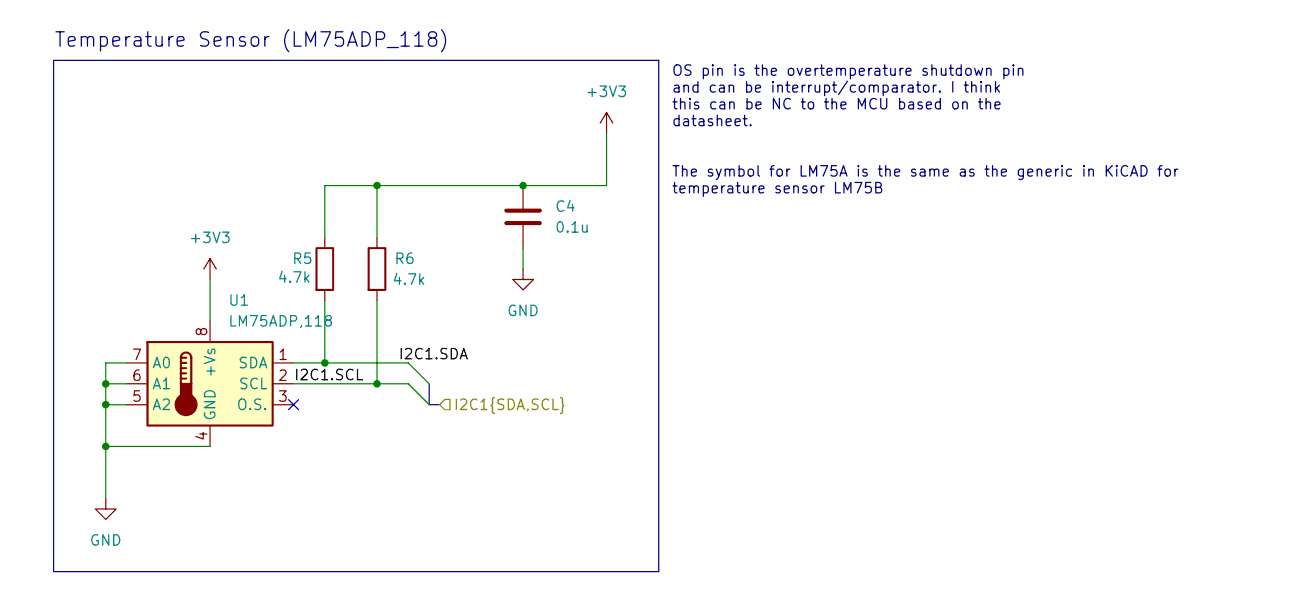
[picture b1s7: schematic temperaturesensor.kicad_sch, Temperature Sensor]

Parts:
C4: 0.1u; C_0402_1005Metric; Manufacturer P/N 0402B104K160HI
R5, R6: 4.7k; R_0402_1005Metric; Manufacturer P/N RK73H1ETTP4701F
U1: LM75ADP,118; SOP65P490X110-8N; Manufacturer P/N LM75ADP,118

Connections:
+3V3: C4.1, R5.1, R6.1, U1.8 (+Vs); also elsewhere on the board
/Temperature Sensor/I2C1.SCL: R6.2, U1.2 (SCL); also elsewhere on the board
/Temperature Sensor/I2C1.SDA: R5.2, U1.1 (SDA); also elsewhere on the board
GND: C4.2, U1.4 (GND), U1.5 (A2), U1.6 (A1), U1.7 (A0); also elsewhere on the board

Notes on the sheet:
OS pin is the overtemperature shutdown pin and can be interrupt/comparator. I think this can be NC to the MCU based on the datasheet. The symbol for LM75A is the same as the generic in KiCAD for temperature sensor LM75B
Temperature Sensor (LM75ADP_118)

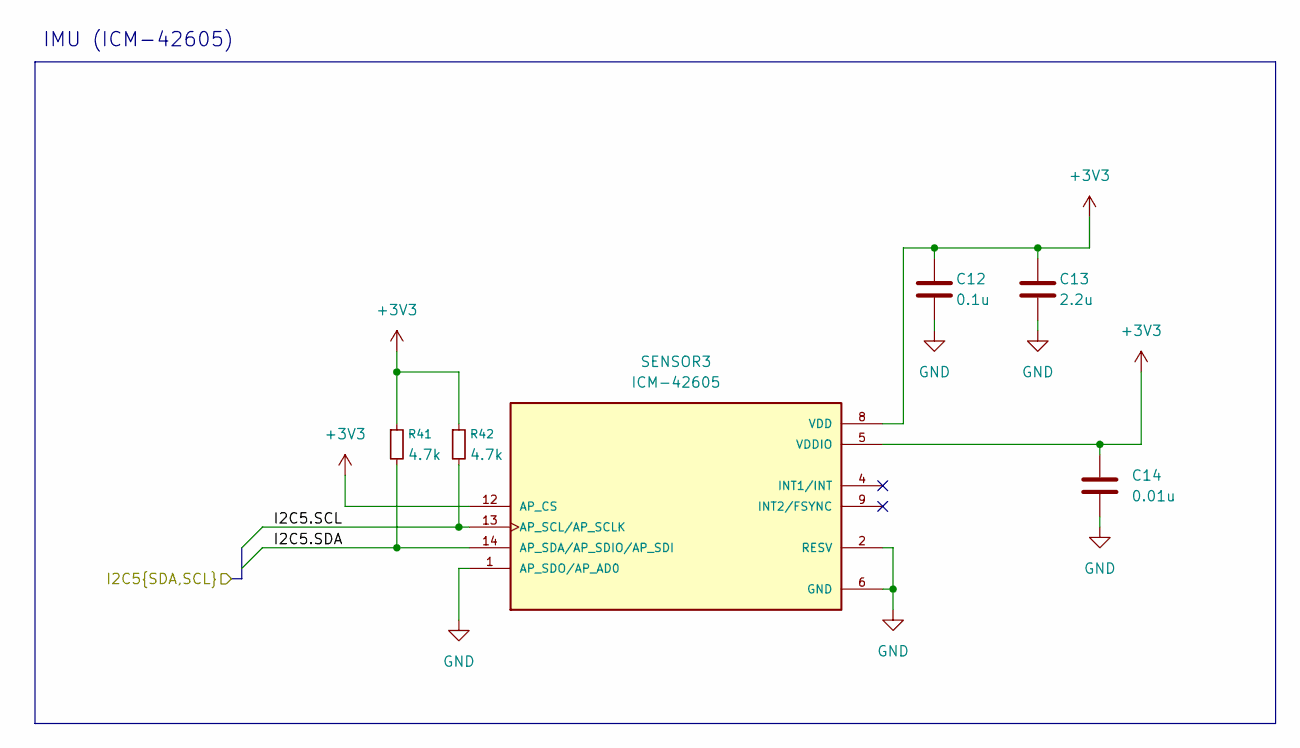
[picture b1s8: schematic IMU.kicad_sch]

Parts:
C12: 0.1u; C_0402_1005Metric; Manufacturer P/N 0402B104K160HI
C13: 2.2u; C_0402_1005Metric; Manufacturer P/N 0402W225K100HI
C14: 0.01u; C_0402_1005Metric; Manufacturer P/N 0402B103K500HI
R41, R42: 4.7k; R_0402_1005Metric; Manufacturer P/N RK73H1ETTP4701F
SENSOR3: ICM-42605; XDCR_ICM-42605; Manufacturer P/N 1428-1152-2-ND

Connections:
+3V3: C12.1, C13.1, C14.1, R41.1, R42.1, SENSOR3.5 (VDDIO), SENSOR3.8 (VDD), SENSOR3.12 (AP_CS); also elsewhere on the board
/IMU/I2C5.SCL: R42.2, SENSOR3.13 (AP_SCL/AP_SCLK); also elsewhere on the board
/IMU/I2C5.SDA: R41.2, SENSOR3.14 (AP_SDA/AP_SDIO/AP_SDI); also elsewhere on the board
GND: C12.2, C13.2, C14.2, SENSOR3.1 (AP_SDO/AP_AD0), SENSOR3.2 (RESV), SENSOR3.3 (RESV), SENSOR3.6 (GND), SENSOR3.7 (RESV), SENSOR3.10 (RESV), SENSOR3.11 (RESV); also elsewhere on the board

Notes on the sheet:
IMU (ICM-42605)
